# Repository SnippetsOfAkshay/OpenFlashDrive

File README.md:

# 💾 OpenFlashDrive
A from-scratch USB-C mass-storage device built around the Prolific PL2732 USB 3.0-to-eMMC controller, with two 64 GB eMMC chips presented to the host as a single 128 GB volume.

Status: schematic and PCB design study · EDA: KiCad 10.0.5 · Link speed: USB 3.0 SuperSpeed (5 Gbps), USB 2.0 fallback

---

## 📋 Overview

A complete schematic capture of a USB 3.0 flash drive, built to learn how storage, high-speed USB, USB-C orientation handling, power distribution, and ESD protection come together on one board.

The design is a hierarchical, multi-sheet KiCad schematic. It is the design only: nothing here has been fabricated or brought up on hardware yet.

What it does:
- Two 64 GB eMMC devices combined into one ~128 GB USB storage volume (JBOD)
- Full USB-C support: reversible orientation, SuperSpeed and USB 2.0, CC detection
- Dedicated ESD and VBUS protection on every externally exposed line
- A regulated power tree feeding the controller and memory from a single 5 V input

---

## 💸 Why this exists

A finished 128 GB USB-C drive sells for about $27. The parts to build one as an individual, ordering a single unit, come to roughly $110-120. The two most important chips, the controller and the memory, aren't stocked at the usual Western catalog distributors at all, and most of that cost is the memory.

This exists to show what goes into a device people treat as disposable, and what low-volume hardware sourcing looks like.

---

## 🏗️ System architecture

Signal path, following the data from the plug inward:

Key points the schematic makes explicit:
- ESD protection and VBUS protection run on separate paths. TVS arrays clamp the data lines; a separate device limits current and guards the VBUS rail. Signal and power are protected independently.
- One chip, the HD3SS3220, handles both orientation detection and SuperSpeed muxing. It reads CC1/CC2 to find the plug orientation, then switches the SuperSpeed TX/RX pairs so the controller always sees them correctly, whichever way the cable went in.
- USB 2.0 skips the mux. Only the SuperSpeed pairs need orientation switching, so the D+/D- lines route straight to the controller.
- The controller generates most of its own rails and takes a 1.2 V core voltage from the external buck off the protected VBUS.

---

## 🧩 Key components

| Ref | Part | Function |
|-----|------|----------|
| U1 | Prolific **PL2732** | USB 3.0-to-eMMC storage controller (the bridge) |
| U2, U3 | FORESEE **FEMDNN064G-C9A61** | 64 GB eMMC devices (×2, combined to 128 GB) |
| U4 | TI **HD3SS3220** | USB-C orientation detection + SuperSpeed mux |
| U8 | TI **TPD1S514** | VBUS protection and current limiting |
| U5, U6, U7, U9 | TI **TPD4EUSB30** | ESD / TVS arrays on high-speed data lines |
| U10 | TI **TPS62807** | Step-down buck for the 1.2 V core rail |
| Y1 | Abracon **ABM8W-30.000MHZ** | 30 MHz reference crystal |
| J1 | **USB4155-03-C** | USB Type-C receptacle |
| U11 | **AT25XE512C** | Optional SPI flash for firmware/config (DNP, write-disabled) |

---

## ⚡ Power architecture

A single 5 V USB VBUS input is protected, then regulated into the rails the board needs:

| Rail | Source | Used by |
|------|--------|---------|
| VBUS 5 V (protected) | TPD1S514 from USB VBUS | Buck input, controller |
| 1.2 V core | TPS62807 buck (1 µH, ~0.2 A) | PL2732 core |
| 3.3 V | Controller-generated | eMMC core, SPI flash |
| 1.8 V | Controller-generated | eMMC I/O |

The 1.2 V core rail was validated in TI WebBench before the layout was committed, holding roughly 1.27-1.34 V across the load range in simulation. Local high-frequency decoupling sits at the controller, mux, memory, and regulator.

---

## 📑 Schematic sheets

Hierarchical design, one concern per sheet:

| # | Sheet | Contents |
|---|-------|----------|
| 1 | Root | Top-level block interconnect |
| 2 | USB_CONNECTOR | USB-C receptacle, TVS arrays, TPD1S514, HD3SS3220 mux |
| 3 | USB_FLASH_CONTROLLER | PL2732, crystal, reset, decoupling |
| 4 | eMMC_BANK | Two 64 GB eMMC devices, separate clock/command per device |
| 5 | POWER | TPS62807 buck + WebBench simulation reference |
| 6 | SPI_FLASH | Optional AT25XE512C (DNP) |

The full schematic is in [`USB-TO-MEM.pdf`](USB-TO-MEM.pdf), with source files under the KiCad project.

---

## 📶 Signal integrity & layout notes

- Controlled-impedance routing for the high-speed USB pairs, targeting ~90 Ω differential
- Each eMMC device has its own dedicated command and clock channels and an 8-bit data path
- Separate power and ground strategy for the high-speed digital interfaces
- Connector shield tied to system ground

---

## 📁 Repository structure

```
OpenFlashDrive/
├── README.md
├── USB-TO-MEM.pdf              # Full schematic (all sheets)
├── CAD Files/
│   ├── USB-TO-MEM.kicad_pro    # KiCad project
│   ├── USB-TO-MEM.kicad_sch    # Root schematic
│   ├── *.kicad_sch             # Hierarchical sheets
└──  docs/
    └── board-render.png        # 3D render

```

*(Adjust to match your actual folders as you add files.)*

---

## 🛠️ Opening the project

Built in KiCad 10.0.5. Clone the repo and open `hardware/USB-TO-MEM.kicad_pro` in KiCad 10 or later.

```bash
git clone https://github.com/SnippetsOfAkshay/OpenFlashDrive.git
```

---

## 🚧 Project status

This is a design study. The schematic is complete; the board hasn't been fabricated, assembled, or tested on hardware. Expect some assumptions (impedance targets, power behavior, footprint choices) to need revision on the first spin.

---

## ⚠️ Disclaimer

A personal reference design, shared for learning. It hasn't been validated on physical hardware. If you reuse any of it, check every rail, footprint, and impedance target against the current datasheets before fabrication.

---

## 📜 License

Pick a license before publishing. For a design meant to be learned from and reused, [MIT](https://choosealicense.com/licenses/mit/) (permissive) or [CERN-OHL-S](https://choosealicense.com/licenses/cern-ohl-s-2.0/) (open hardware, share-alike) both work.

---

## 👤 Author

Akshay · https://www.linkedin.com/in/akshaymomaya/

Spot a mistake or have a better way to do something? Open an issue. Corrections welcome.

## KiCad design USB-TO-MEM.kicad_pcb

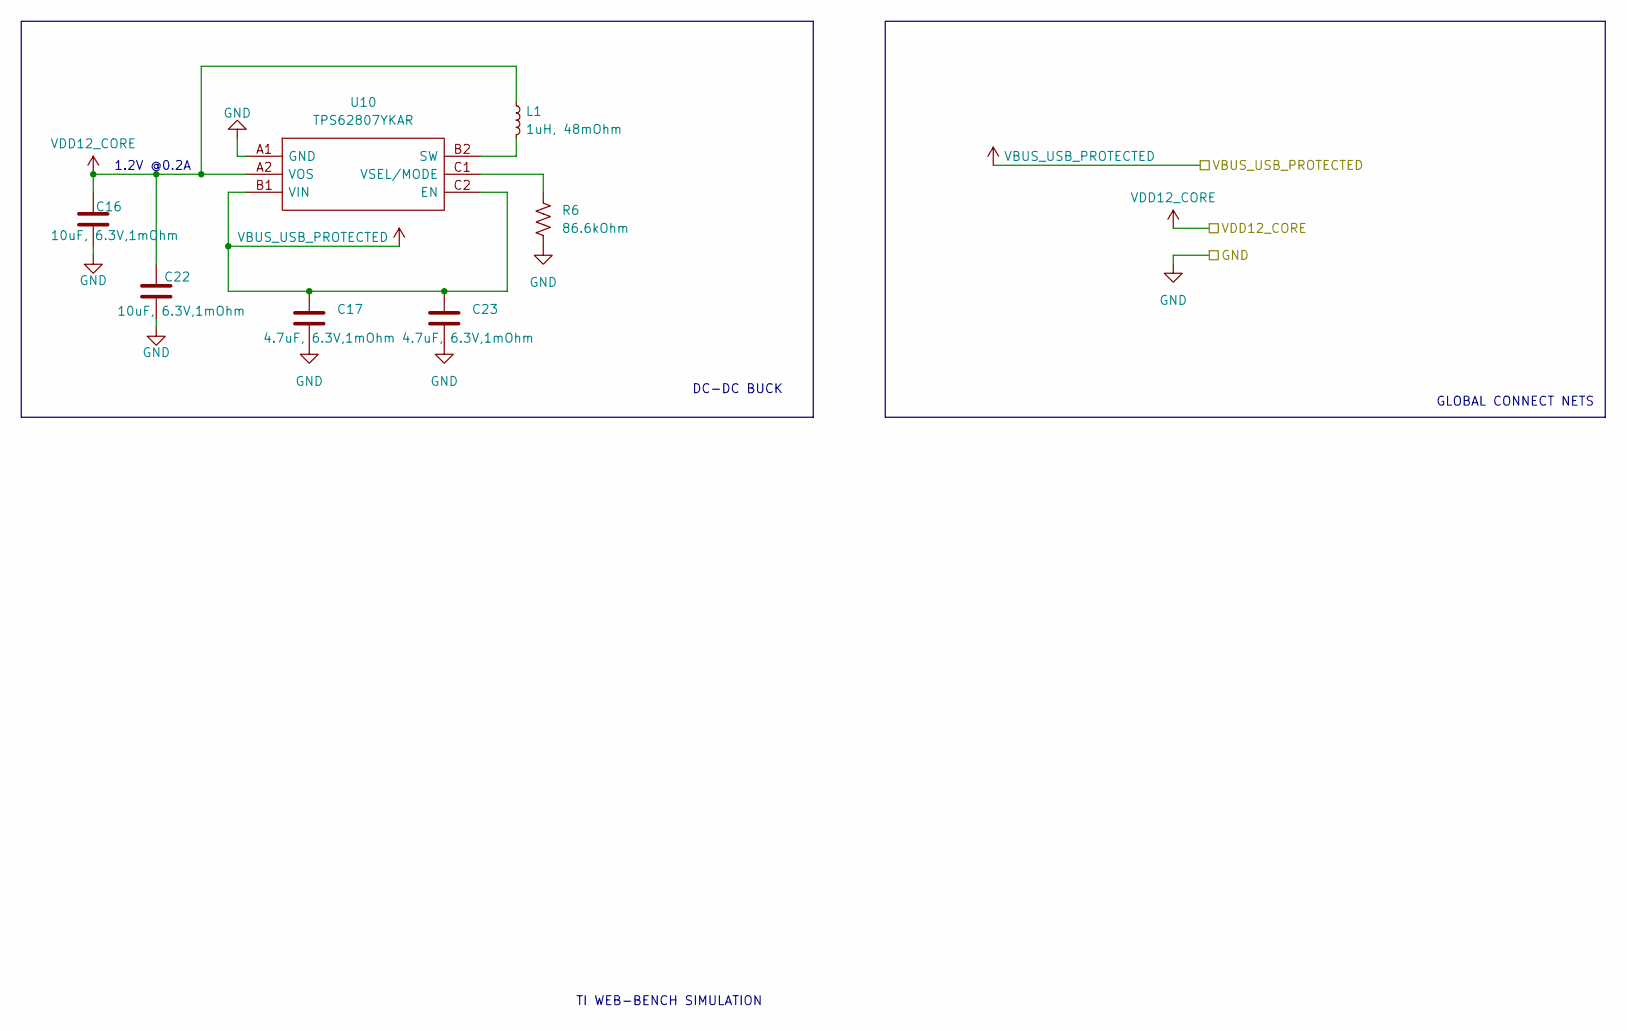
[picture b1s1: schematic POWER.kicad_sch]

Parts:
C16, C22: 10uF, 6.3V,1mOhm; C_0201_0603Metric
C17, C23: 4.7uF, 6.3V,1mOhm; C_0201_0603Metric
L1: 1uH, 48mOhm; L_0402_1005Metric
R6: 86.6kOhm; R_0201_0603Metric
U10: TPS62807YKAR

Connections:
GND: C16.2, C17.2, C22.2, C23.2, R6.2, U10.A1 (GND); also elsewhere on the board
unnamed: L1.2, U10.B2 (SW)
unnamed: R6.1, U10.C1 (VSEL/MODE)
VBUS_USB_PROTECTED: C17.1, C23.1, U10.B1 (VIN), U10.C2 (EN); also elsewhere on the board
VDD12_CORE: C16.1, C22.1, L1.1, U10.A2 (VOS); also elsewhere on the board

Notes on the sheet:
GLOBAL CONNECT NETS
TI WEB-BENCH SIMULATION
DC-DC BUCK
1.2V @0.2A

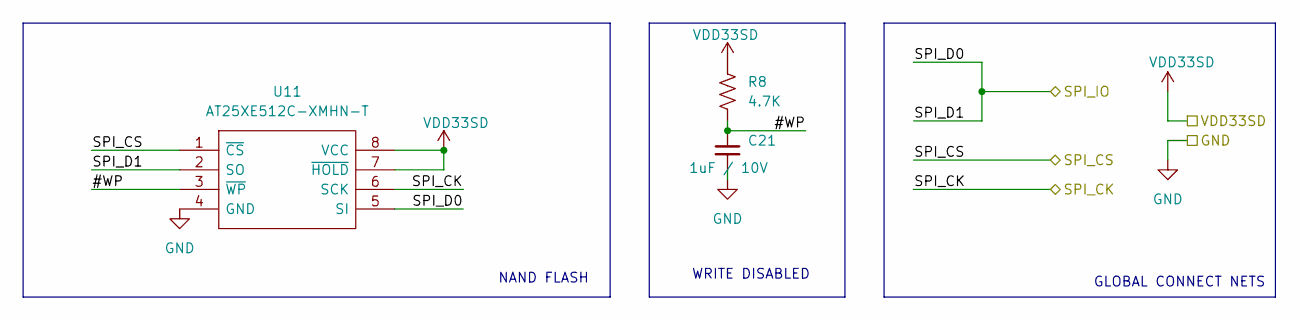
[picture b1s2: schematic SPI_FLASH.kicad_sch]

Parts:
C21: 1uF / 10V; C_0201_0603Metric
R8: 4.7K; R_0201_0603Metric
U11: AT25XE512C-XMHN-T; SOP65P640X120-8N

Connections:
/SPI_FLASH/#WP: C21.1, R8.2, U11.3 (~WP)
/SPI_FLASH/SPI_CK: U11.6 (SCK); also elsewhere on the board
/SPI_FLASH/SPI_CS: U11.1 (~CS); also elsewhere on the board
/SPI_FLASH/SPI_D0: U11.2 (SO), U11.5 (SI); also elsewhere on the board
VBUS_USB_PROTECTED: C21.2, U11.4 (GND); also elsewhere on the board
VDD33SD: R8.1, U11.7 (~HOLD), U11.8 (VCC); also elsewhere on the board

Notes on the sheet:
WRITE DISABLED
NAND FLASH
GLOBAL CONNECT NETS

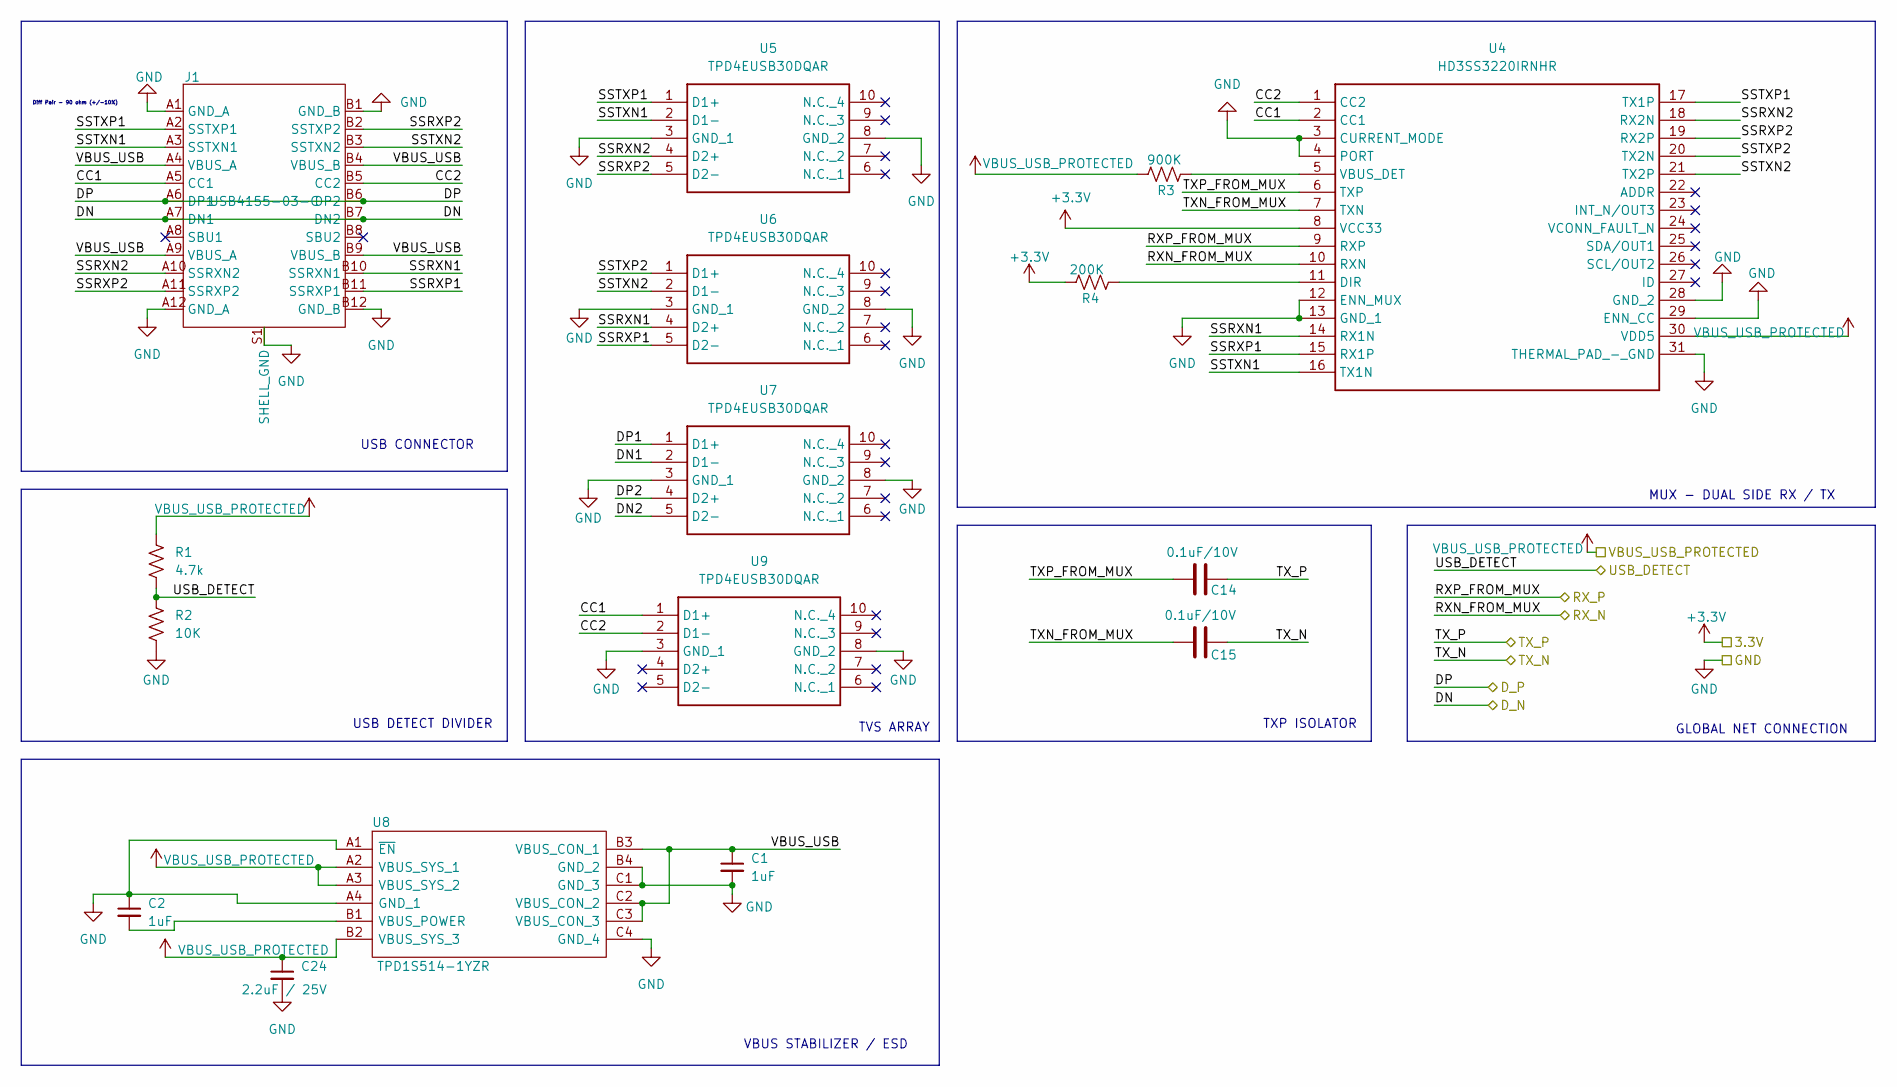
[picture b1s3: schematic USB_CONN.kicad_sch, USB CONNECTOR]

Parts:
C1, C2: 1uF; C_0201_0603Metric
C14, C15: 0.1uF/10V; C_0201_0603Metric
C24: 2.2uF / 25V; C_0201_0603Metric
J1: USB4155-03-C; CONN_USB4155_GCT
R1: 4.7k; R_0201_0603Metric
R2: 10K; R_0201_0603Metric
R3: 900K; R_0201_0603Metric
R4: 200K; R_0201_0603Metric
U4: HD3SS3220IRNHR; Mouser Part Number 595-HD3SS3220IRNHR
U5, U6, U7, U9: TPD4EUSB30DQAR; DQA_R-PUSON-N10_; Mouser Part Number 595-TPD4EUSB30DQAR
U8: TPD1S514-1YZR; BGA12C40P4X3_199X129X62

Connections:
+3.3V: R4.1, U4.8 (VCC33); also elsewhere on the board
/USB_CONNECTOR/CC1: J1.A5 (CC1), U4.2 (CC1), U9.1 (D1+)
/USB_CONNECTOR/CC2: J1.B5 (CC2), U4.1 (CC2), U9.2 (D1-)
/USB_CONNECTOR/DN: J1.A7 (DN1), J1.B7 (DN2); also elsewhere on the board
/USB_CONNECTOR/DN1: U7.2 (D1-)
/USB_CONNECTOR/DN2: U7.5 (D2-)
/USB_CONNECTOR/DP: J1.A6 (DP1), J1.B6 (DP2); also elsewhere on the board
/USB_CONNECTOR/DP1: U7.1 (D1+)
/USB_CONNECTOR/DP2: U7.4 (D2+)
/USB_CONNECTOR/RXN_FROM_MUX: U4.10 (RXN); also elsewhere on the board
/USB_CONNECTOR/RXP_FROM_MUX: U4.9 (RXP); also elsewhere on the board
/USB_CONNECTOR/SSRXN1: J1.B10 (SSRXN1), U4.14 (RX1N), U6.4 (D2+)
/USB_CONNECTOR/SSRXN2: J1.A10 (SSRXN2), U4.18 (RX2N), U5.4 (D2+)
/USB_CONNECTOR/SSRXP1: J1.B11 (SSRXP1), U4.15 (RX1P), U6.5 (D2-)
/USB_CONNECTOR/SSRXP2: J1.A11 (SSRXP2), J1.B2 (SSTXP2), U4.19 (RX2P), U5.5 (D2-)
/USB_CONNECTOR/SSTXN1: J1.A3 (SSTXN1), U4.16 (TX1N), U5.2 (D1-)
/USB_CONNECTOR/SSTXN2: J1.B3 (SSTXN2), U4.21 (TX2P), U6.2 (D1-)
/USB_CONNECTOR/SSTXP1: J1.A2 (SSTXP1), U4.17 (TX1P), U5.1 (D1+)
/USB_CONNECTOR/SSTXP2: U4.20 (TX2N), U6.1 (D1+)
/USB_CONNECTOR/TXN_FROM_MUX: C15.1, U4.7 (TXN)
/USB_CONNECTOR/TXP_FROM_MUX: C14.1, U4.6 (TXP)
/USB_CONNECTOR/TX_N: C15.2; also elsewhere on the board
/USB_CONNECTOR/TX_P: C14.2; also elsewhere on the board
/USB_CONNECTOR/USB_DETECT: R1.2, R2.1; also elsewhere on the board
/USB_CONNECTOR/VBUS_USB: C1.1, J1.A4 (VBUS_A), J1.A9 (VBUS_A), J1.B4 (VBUS_B), J1.B9 (VBUS_B), U8.B3 (VBUS_CON_1), U8.C2 (VBUS_CON_2), U8.C3 (VBUS_CON_3)
GND: C1.2, C2.1, C24.2, J1.A1 (GND_A), J1.A12 (GND_A), J1.B1 (GND_B), J1.B12 (GND_B), J1.S1 (SHELL_GND), R2.2, U4.3 (CURRENT_MODE), U4.4 (PORT), U4.12 (ENN_MUX), U4.13 (GND_1), U4.28 (GND_2), U4.29 (ENN_CC), U4.31 (THERMAL_PAD_-_GND), U5.3 (GND_1), U5.8 (GND_2), U6.3 (GND_1), U6.8 (GND_2), U7.3 (GND_1), U7.8 (GND_2), U8.A1 (~EN), U8.A4 (GND_1), U8.B4 (GND_2), U8.C1 (GND_3), U8.C4 (GND_4), U9.3 (GND_1), U9.8 (GND_2); also elsewhere on the board
unnamed: R4.2, U4.11 (DIR)
unnamed: R3.2, U4.5 (VBUS_DET)
unnamed: C2.2, U8.B1 (VBUS_POWER)
VBUS_USB_PROTECTED: C24.1, R1.1, R3.1, U4.30 (VDD5), U8.A2 (VBUS_SYS_1), U8.A3 (VBUS_SYS_2), U8.B2 (VBUS_SYS_3); also elsewhere on the board

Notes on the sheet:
USB DETECT DIVIDER
USB CONNECTOR
Diff Pair - 90 ohm (+/-10%)
MUX - DUAL SIDE RX / TX
TXP ISOLATOR
TVS ARRAY
GLOBAL NET CONNECTION
VBUS STABILIZER / ESD

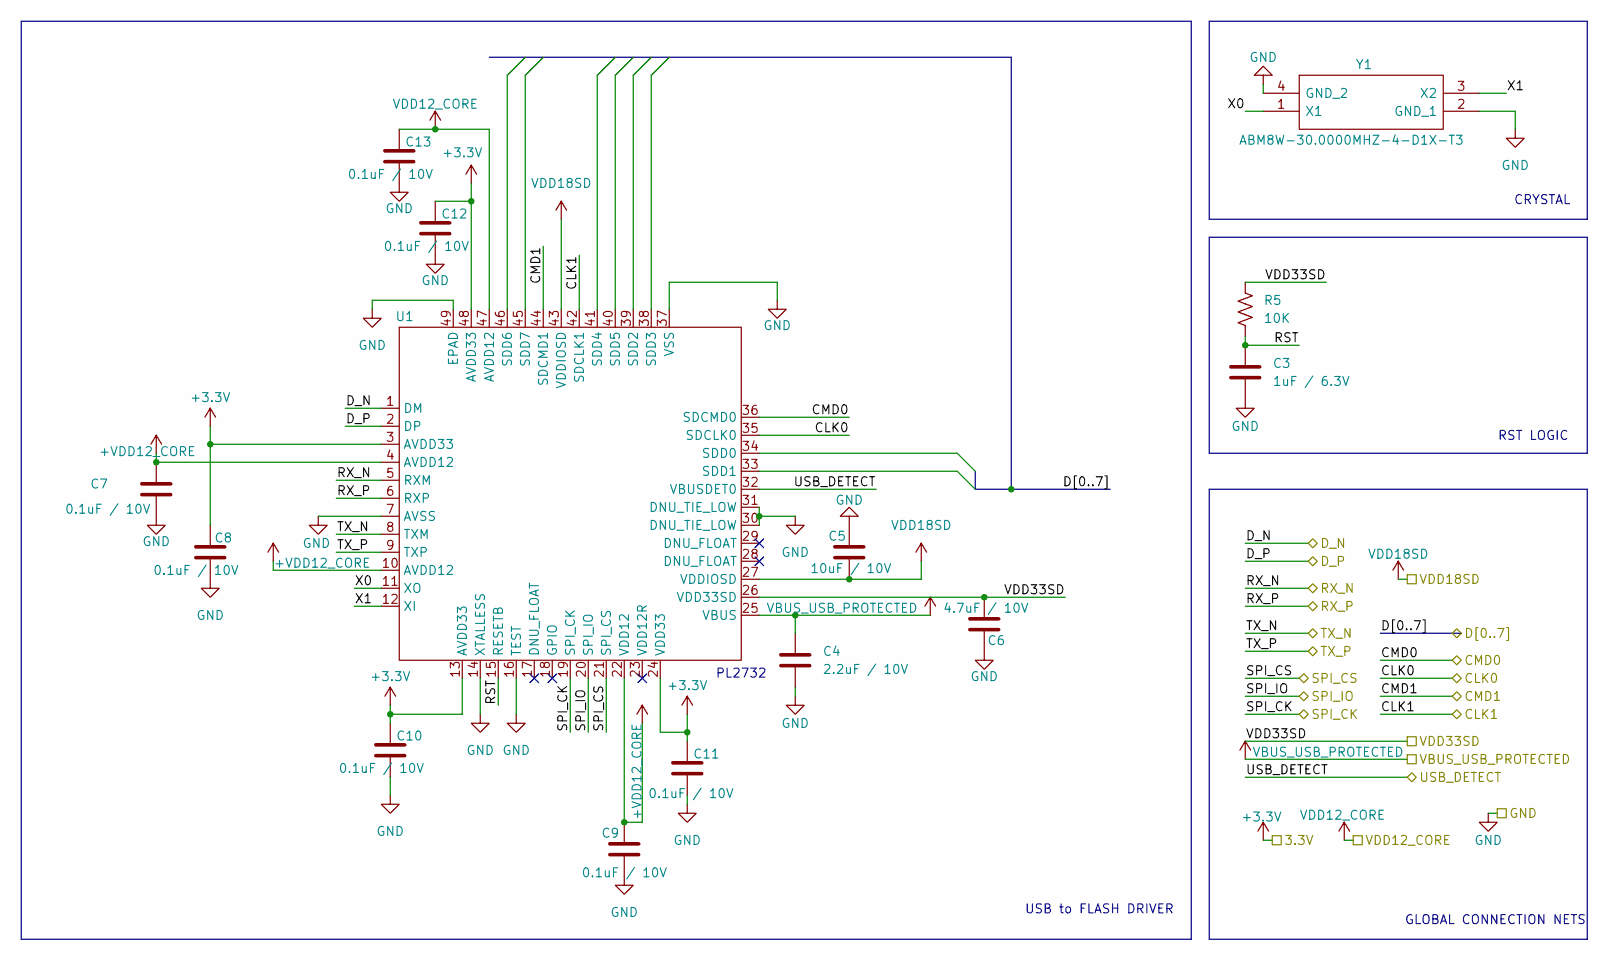
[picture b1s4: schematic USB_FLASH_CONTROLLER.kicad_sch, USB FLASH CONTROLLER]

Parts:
C3: 1uF / 6.3V; C_0201_0603Metric
C4: 2.2uF / 10V; C_0201_0603Metric
C5: 10uF / 10V; C_0201_0603Metric
C6: 4.7uF / 10V; C_0201_0603Metric
C7, C8, C9, C10, C11, C12, C13: 0.1uF / 10V; C_0201_0603Metric
R5: 10K; R_0201_0603Metric
U1: PL2732; QFP-48_7x7_Pitch0.5mm
Y1: ABM8W-30.0000MHZ-4-D1X-T3; ABM8W480000MHZ6D1XT3

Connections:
+1V8: C5.2, U1.27 (VDDIOSD), U1.43 (VDDIOSD); also elsewhere on the board
+3.3V: C8.1, C10.1, C11.1, C12.1, U1.3 (AVDD33), U1.13 (AVDD33), U1.24 (VDD33), U1.48 (AVDD33); also elsewhere on the board
+VDD12_CORE: C7.1, C9.1, U1.4 (AVDD12), U1.10 (AVDD12), U1.22 (VDD12)
/SPI_FLASH/SPI_CK: U1.19 (SPI_CK); also elsewhere on the board
/SPI_FLASH/SPI_CS: U1.21 (SPI_CS); also elsewhere on the board
/SPI_FLASH/SPI_D0: U1.20 (SPI_IO); also elsewhere on the board
/USB_CONNECTOR/DN: U1.1 (DM); also elsewhere on the board
/USB_CONNECTOR/DP: U1.2 (DP); also elsewhere on the board
/USB_CONNECTOR/RXN_FROM_MUX: U1.5 (RXM); also elsewhere on the board
/USB_CONNECTOR/RXP_FROM_MUX: U1.6 (RXP); also elsewhere on the board
/USB_CONNECTOR/TX_N: U1.8 (TXM); also elsewhere on the board
/USB_CONNECTOR/TX_P: U1.9 (TXP); also elsewhere on the board
/USB_CONNECTOR/USB_DETECT: U1.32 (VBUSDET0); also elsewhere on the board
/USB_FLASH_CONTROLLER/CLK0: U1.35 (SDCLK0); also elsewhere on the board
/USB_FLASH_CONTROLLER/CLK1: U1.42 (SDCLK1); also elsewhere on the board
/USB_FLASH_CONTROLLER/CMD0: U1.36 (SDCMD0); also elsewhere on the board
/USB_FLASH_CONTROLLER/CMD1: U1.44 (SDCMD1); also elsewhere on the board
/USB_FLASH_CONTROLLER/RST: C3.1, R5.2, U1.15 (RESETB)
/USB_FLASH_CONTROLLER/X0: U1.11 (XO), Y1.1 (X1)
/USB_FLASH_CONTROLLER/X1: U1.12 (XI), Y1.3 (X2)
GND: C3.2, C4.2, C5.1, C6.1, C7.2, C8.2, C9.2, C10.2, C11.2, C12.2, C13.2, U1.7 (AVSS), U1.14 (XTALLESS), U1.16 (TEST), U1.30 (DNU_TIE_LOW), U1.31 (DNU_TIE_LOW), U1.37 (VSS), U1.49 (EPAD), Y1.2 (GND_1), Y1.4 (GND_2); also elsewhere on the board
VBUS_USB_PROTECTED: C4.1, U1.25 (VBUS); also elsewhere on the board
VDD12_CORE: C13.1, U1.47 (AVDD12); also elsewhere on the board
VDD33SD: C6.2, R5.1, U1.26 (VDD33SD); also elsewhere on the board

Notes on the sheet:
RST LOGIC
USB to FLASH DRIVER
PL2732
GLOBAL CONNECTION NETS
CRYSTAL

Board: 6 copper layers, 46 parts (13 on the bottom side), 54 nets, no tracks yet.

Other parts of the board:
C18, C19: 0.1uF, 10V; C_0201_0603Metric
C20: 1uF, 10V; C_0201_0603Metric
R7: 10K; R_0201_0603Metric
U2, U3: FEMDNN064G-C9A61; FBGA153_C_ISI

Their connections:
+1V8: U2.C6 (VCCQ), U2.M4 (VCCQ), U2.N4 (VCCQ), U2.P3 (VCCQ), U2.P5 (VCCQ), U3.C6 (VCCQ), U3.M4 (VCCQ), U3.N4 (VCCQ), U3.P3 (VCCQ), U3.P5 (VCCQ); also elsewhere on the board
/USB_FLASH_CONTROLLER/CLK0: U2.M5 (CMD); also elsewhere on the board
/USB_FLASH_CONTROLLER/CLK1: U3.M6 (CLK); also elsewhere on the board
/USB_FLASH_CONTROLLER/CMD0: U2.M6 (CLK); also elsewhere on the board
/USB_FLASH_CONTROLLER/CMD1: U3.M5 (CMD); also elsewhere on the board
/USB_FLASH_CONTROLLER/D0: U2.A3 (DAT0), U3.A3 (DAT0)
/USB_FLASH_CONTROLLER/D1: U2.A4 (DAT1), U3.A4 (DAT1)
/USB_FLASH_CONTROLLER/D2: U2.A5 (DAT2), U3.A5 (DAT2)
/USB_FLASH_CONTROLLER/D3: U2.B2 (DAT3), U3.B2 (DAT3)
/USB_FLASH_CONTROLLER/D4: U2.B3 (DAT4), U3.B3 (DAT4)
/USB_FLASH_CONTROLLER/D5: U2.B4 (DAT5), U3.B4 (DAT5)
/USB_FLASH_CONTROLLER/D6: U2.B5 (DAT6), U3.B5 (DAT6)
/USB_FLASH_CONTROLLER/D7: U2.B6 (DAT7), U3.B6 (DAT7)
/eMMC_BANK/ERST: C20.1, R7.2, U2.K5 (RST_N), U3.K5 (RST_N)
GND: C18.2, C19.2, C20.2, U2.A6 (VSS), U2.C4 (VSSQ), U2.E7 (VSS), U2.G5 (VSS), U2.H10 (VSS), U2.J5 (VSS), U2.K8 (VSS), U2.N2 (VSSQ), U2.N5 (VSSQ), U2.P4 (VSSQ), U2.P6 (VSSQ), U3.A6 (VSS), U3.C4 (VSSQ), U3.E7 (VSS), U3.G5 (VSS), U3.H10 (VSS), U3.J5 (VSS), U3.K8 (VSS), U3.N2 (VSSQ), U3.N5 (VSSQ), U3.P4 (VSSQ), U3.P6 (VSSQ); also elsewhere on the board
unnamed: C18.1, U2.C2 (VDDI)
unnamed: C19.1, U3.C2 (VDDI)
VDD33SD: R7.1, U2.E6 (VCC), U2.F5 (VCC), U2.J10 (VCC), U2.K9 (VCC), U3.E6 (VCC), U3.F5 (VCC), U3.J10 (VCC), U3.K9 (VCC); also elsewhere on the board
